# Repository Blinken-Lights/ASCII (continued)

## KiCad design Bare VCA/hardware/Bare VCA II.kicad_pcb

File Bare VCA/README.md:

# Bare VCA

Basic linear VCA based on LM13700. Similar to many schematics out there - but set up the way I like it.

6 x VCA and mixer, with built in clipping warning LEDs on the master output.

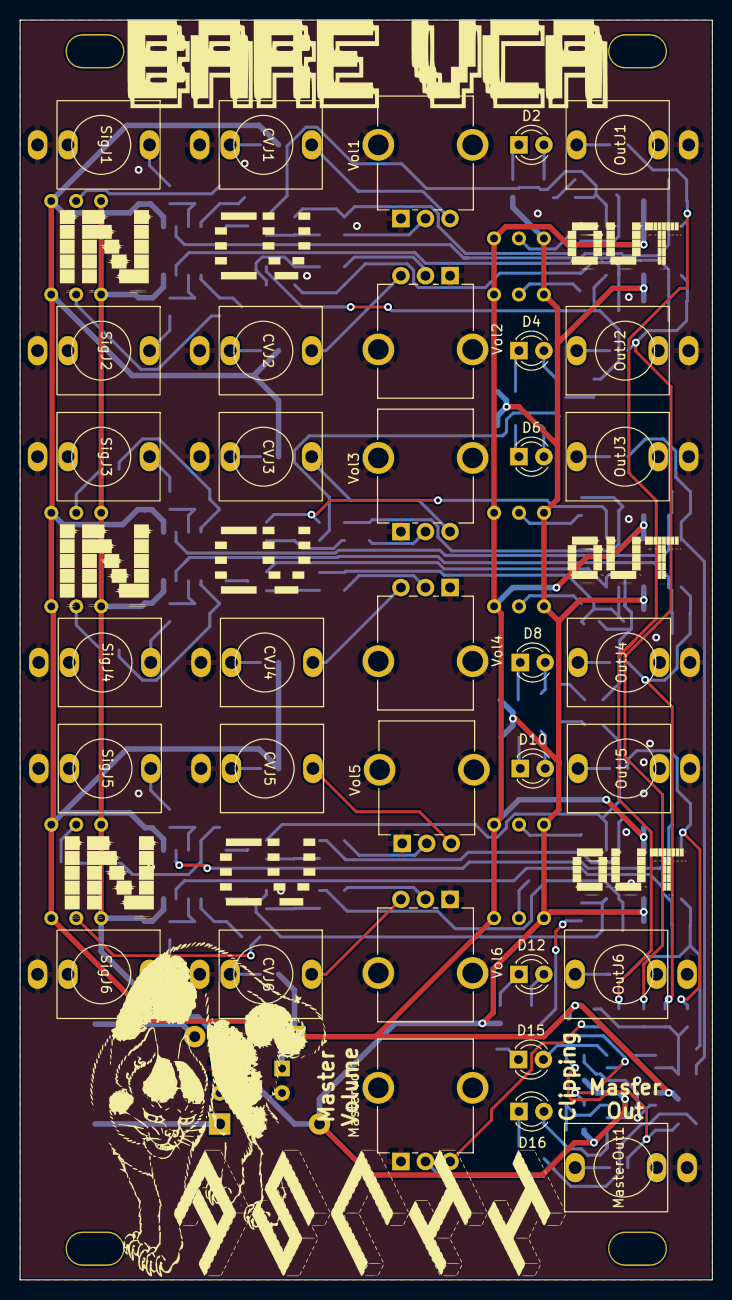
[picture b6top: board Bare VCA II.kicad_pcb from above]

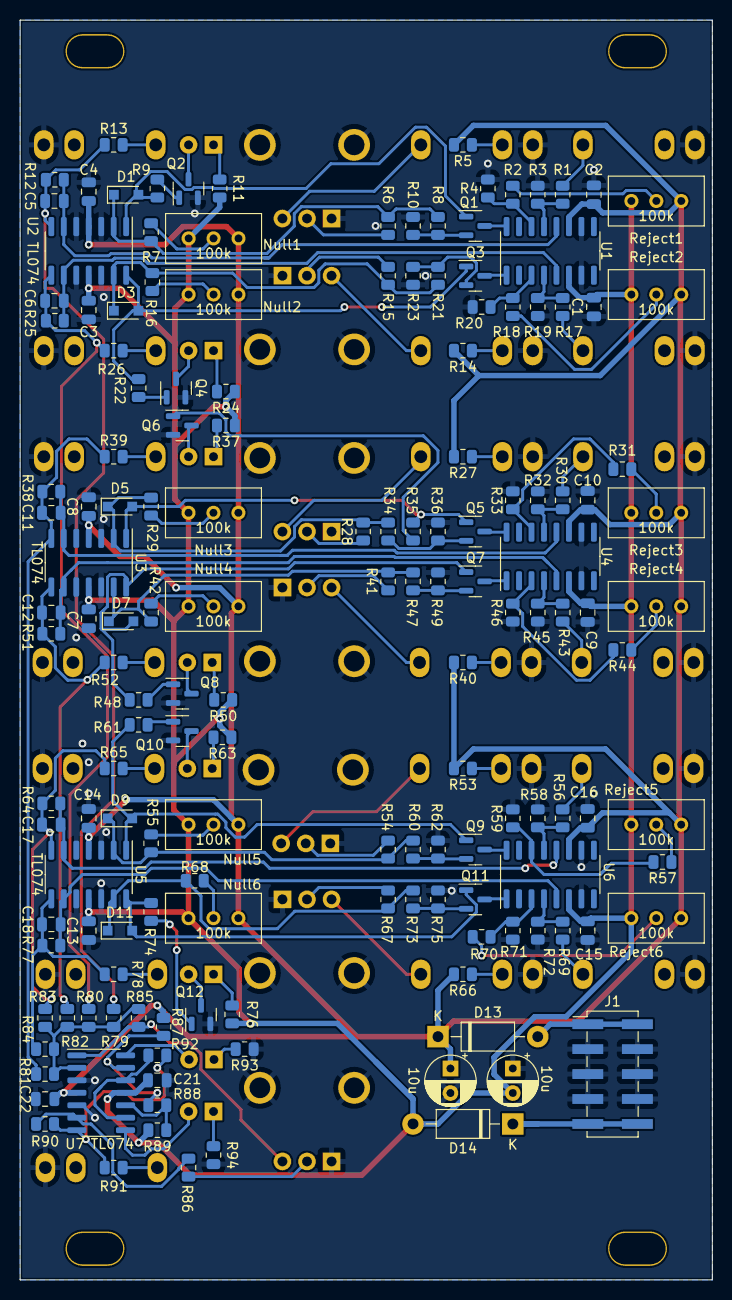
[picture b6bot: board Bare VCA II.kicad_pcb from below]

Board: 2 copper layers, 70.5 x 128.3 mm, 190 parts (156 on the bottom side), 126 nets.

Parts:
C1, C2, C3, C4, C7, C8, C9, C10, C13, C14, C15, C16, C21, C22: 100n; C_0805_2012Metric
C5, C6, C11, C12, C17, C18: 47p; C_0805_2012Metric
C19, C20: 10u; CP_Radial_D5.0mm_P2.50mm
CVJ1, CVJ2, CVJ3, CVJ4, CVJ5, CVJ6: Thonkiconn
D1, D3, D5, D7, D9, D11: 1N4148WS; D_SOD-323_HandSoldering
D2, D6, D10, D15: Red LED; LED_D3.0mm
D4, D8, D12, D16: Blue LED; LED_D3.0mm
D13, D14: 1N5817; D_DO-41_SOD81_P10.16mm_Horizontal
J1: Power; PinHeader_2x05_P2.54mm_Vertical_SMD
MasterOut1: Thonkiconn
MasterVol1: 100k; Potentiometer_GND_Alpha_RD901F-40-00D_Single_Vertical_Circu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
Null1, Null2, Null3, Null4, Null5, Null6: 100k; Potentiometer_Bourns_3296W_Vertical
OutJ1, OutJ2, OutJ3, OutJ4, OutJ5, OutJ6: Thonkiconn
Q1, Q2, Q3, Q4, Q5, Q6, Q7, Q8, Q9, Q10, Q11, Q12: MMBT3906; SOT-23
R1, R2, R6, R8, R12, R15, R17, R18, R21, R25, R28, R30, R31, R34, R38, R41, R43, R44, R47, R51, R54, R56, R57, R60, R64, R67, R69, R70, R73, R77, R79, R80, R81, R82, R83, R84, R86, R87, R89, R92: 100k; R_0805_2012Metric
R3, R4, R19, R20, R32, R33, R45, R46, R58, R59, R71, R72: 220; R_0805_2012Metric
R5, R14, R27, R40, R53, R66: 68k; R_0805_2012Metric
R7, R16, R29, R42, R55, R68: 200k; R_0805_2012Metric
R9, R22, R35, R48, R61, R74: 270k; R_0805_2012Metric
R10, R23, R36, R49, R62, R75: 22k; R_0805_2012Metric
R11, R24, R37, R50, R63, R76: 560; R_0805_2012Metric
R13, R26, R39, R52, R65, R78, R91: 1k; R_0805_2012Metric
R85: 33k; R_0805_2012Metric
R88: 820k; R_0805_2012Metric
R90: 330k; R_0805_2012Metric
R93, R94: 10k; R_0805_2012Metric
Reject1, Reject2, Reject3, Reject4, Reject5, Reject6: 100k; Potentiometer_Bourns_3296W_Vertical
SigJ1, SigJ2, SigJ3, SigJ4, SigJ5, SigJ6: Thonkiconn
U1, U4, U6: LM13700; SOIC-16_3.9x9.9mm_P1.27mm
U2, U3, U5, U7: TL074; SOIC-14_3.9x8.7mm_P1.27mm
Vol1, Vol2, Vol3, Vol4, Vol5, Vol6: 100k; Potentiometer_GND_Alpha_RD901F-40-00D_Single_Vertical_Circu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

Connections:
+12V: C2.1, C4.1, C8.1, C10.1, C14.1, C16.1, C19.1, C22.1, D13.1 (K), Null1.1, Null2.1, Null3.1, Null4.1, Null5.1, Null6.1, R5.2, R14.2, R27.2, R40.2, R53.2, R66.2, R87.2, Reject1.1, Reject2.1, Reject3.1, Reject4.1, Reject5.1, Reject6.1, U1.11 (V+), U2.4 (V+), U3.4 (V+), U4.11 (V+), U5.4 (V+), U6.11 (V+), U7.4 (V+)
-12V: C1.2, C3.2, C7.2, C9.2, C13.2, C15.2, C20.2, C21.2, D14.2 (A), Null1.3, Null2.3, Null3.3, Null4.3, Null5.3, Null6.3, R11.1, R24.1, R37.1, R50.1, R63.1, R76.1, R89.1, Reject1.3, Reject2.3, Reject3.3, Reject4.3, Reject5.3, Reject6.3, U1.6 (V-), U2.11 (V-), U3.11 (V-), U4.6 (V-), U5.11 (V-), U6.6 (V-), U7.11 (V-)
/2xVCAs1/CV In 1: CVJ3.3, Vol3.3
/2xVCAs1/CV In 2: CVJ4.3, Vol4.3
/2xVCAs1/Output 1: OutJ3.3, R39.2
/2xVCAs1/Output 2: OutJ4.3, R52.2
/2xVCAs1/Raw Output 1: C11.2, R38.2, R39.1, R81.1, U3.7
/2xVCAs1/Raw Output 2: C12.2, R51.2, R52.1, R82.1, U3.8
/2xVCAs1/Signal In 1: R30.1, SigJ3.3
/2xVCAs1/Signal In 2: R43.1, SigJ4.3
/2xVCAs2/CV In 1: CVJ5.3, Vol5.3
/2xVCAs2/CV In 2: CVJ6.3, Vol6.3
/2xVCAs2/Output 1: OutJ5.3, R65.2
/2xVCAs2/Output 2: OutJ6.3, R78.2
/2xVCAs2/Raw Output 1: C17.2, R64.2, R65.1, R83.1, U5.7
/2xVCAs2/Raw Output 2: C18.2, R77.2, R78.1, R84.1, U5.8
/2xVCAs2/Signal In 1: R56.1, SigJ5.3
/2xVCAs2/Signal In 2: R69.1, SigJ6.3
/2xVCAs/CV In 1: CVJ1.3, Vol1.3
/2xVCAs/CV In 2: CVJ2.3, Vol2.3
/2xVCAs/Output 1: OutJ1.3, R13.2
/2xVCAs/Output 2: OutJ2.3, R26.2
/2xVCAs/Raw Output 1: C5.2, R12.2, R13.1, R79.1, U2.7
/2xVCAs/Raw Output 2: C6.2, R25.2, R26.1, R80.1, U2.8
/2xVCAs/Signal In 1: R1.1, SigJ1.3
/2xVCAs/Signal In 2: R17.1, SigJ2.3
GND: C1.1, C2.2, C3.1, C4.2, C7.1, C8.2, C9.1, C10.2, C13.1, C14.2, C15.1, C16.2, C19.2, C20.1, C21.1, C22.2, CVJ1.1, CVJ2.1, CVJ3.1, CVJ4.1, CVJ5.1, CVJ6.1, J1.3, J1.4, J1.5, J1.6, J1.7, J1.8, MasterOut1.1, MasterVol1.1, MasterVol1.4 (GND), OutJ1.1, OutJ2.1, OutJ3.1, OutJ4.1, OutJ5.1, OutJ6.1, Q2.2 (E), Q4.2 (E), Q6.2 (E), Q8.2 (E), Q10.2 (E), Q12.2 (E), R3.1, R4.2, R10.2, R19.1, R20.2, R23.2, R32.1, R33.2, R36.2, R45.1, R46.2, R49.2, R58.1, R59.2, R62.2, R71.1, R72.2, R75.2, R93.1, R94.1, SigJ1.1, SigJ2.1, SigJ3.1, SigJ4.1, SigJ5.1, SigJ6.1, U1.7, U1.10, U2.3 (+), U2.5 (+), U2.10 (+), U2.12 (+), U3.3 (+), U3.5 (+), U3.10 (+), U3.12 (+), U4.7, U4.10, U5.3 (+), U5.5 (+), U5.10 (+), U5.12 (+), U6.7, U6.10, U7.3 (+), U7.5 (+), Vol1.1, Vol1.4 (GND), Vol2.1, Vol2.4 (GND), Vol3.1, Vol3.4 (GND), Vol4.1, Vol4.4 (GND), Vol5.1, Vol5.4 (GND), Vol6.1, Vol6.4 (GND)
unnamed: C5.1, R12.1, U1.12, U2.6 (-)
unnamed: C6.1, R25.1, U1.5, U2.9 (-)
unnamed: C11.1, R38.1, U3.6 (-), U4.12
unnamed: C12.1, R51.1, U3.9 (-), U4.5
unnamed: C17.1, R64.1, U5.6 (-), U6.12
unnamed: C18.1, R77.1, U5.9 (-), U6.5
unnamed: CVJ1.2, R5.1
unnamed: CVJ2.2, R14.1
unnamed: CVJ3.2, R27.1
unnamed: CVJ4.2, R40.1
unnamed: CVJ5.2, R53.1
unnamed: CVJ6.2, R66.1
unnamed: D1.1 (K), R6.2, R7.2, R8.1, U2.2 (-)
unnamed: D1.2 (A), Q1.1 (B), R9.1, U2.1
unnamed: D2.1 (K), R11.2
unnamed: D2.2 (A), Q2.3 (C)
unnamed: D3.1 (K), R15.2, R16.2, R21.1, U2.13 (-)
unnamed: D3.2 (A), Q3.1 (B), R22.1, U2.14
unnamed: D4.1 (K), R24.2
unnamed: D4.2 (A), Q4.3 (C)
unnamed: D5.1 (K), R28.2, R29.2, R34.1, U3.2 (-)
unnamed: D5.2 (A), Q5.1 (B), R35.1, U3.1
unnamed: D6.1 (K), R37.2
unnamed: D6.2 (A), Q6.3 (C)
unnamed: D7.1 (K), R41.2, R42.2, R47.1, U3.13 (-)
unnamed: D7.2 (A), Q7.1 (B), R48.1, U3.14
unnamed: D8.1 (K), R50.2
unnamed: D8.2 (A), Q8.3 (C)
unnamed: D9.1 (K), R54.2, R55.2, R60.1, U5.2 (-)
unnamed: D9.2 (A), Q9.1 (B), R61.1, U5.1
unnamed: D10.1 (K), R63.2
unnamed: D10.2 (A), Q10.3 (C)
unnamed: D11.1 (K), R67.2, R68.2, R73.1, U5.13 (-)
unnamed: D11.2 (A), Q11.1 (B), R74.1, U5.14
unnamed: D12.1 (K), R76.2
unnamed: D12.2 (A), Q12.3 (C)
unnamed: D13.2 (A), J1.1, J1.2
unnamed: D14.1 (K), J1.9, J1.10
unnamed: D15.1 (K), R93.2
unnamed: D15.2 (A), U7.14
unnamed: D16.1 (K), R94.2
unnamed: D16.2 (A), U7.8
unnamed: MasterOut1.3, R91.2
unnamed: MasterVol1.2, R86.1
unnamed: MasterVol1.3, R85.2, U7.1
unnamed: Null1.2, R7.1
unnamed: Null2.2, R16.1
unnamed: Null3.2, R29.1
unnamed: Null4.2, R42.1
unnamed: Null5.2, R55.1
unnamed: Null6.2, R68.1
unnamed: Q1.2 (E), R8.2, R10.1
unnamed: Q1.3 (C), U1.16
unnamed: Q2.1 (B), R9.2
unnamed: Q3.2 (E), R21.2, R23.1
unnamed: Q3.3 (C), U1.1
unnamed: Q4.1 (B), R22.2
unnamed: Q5.2 (E), R34.2, R36.1
unnamed: Q5.3 (C), U4.16
unnamed: Q6.1 (B), R35.2
unnamed: Q7.2 (E), R47.2, R49.1
unnamed: Q7.3 (C), U4.1
unnamed: Q8.1 (B), R48.2
unnamed: Q9.2 (E), R60.2, R62.1
unnamed: Q9.3 (C), U6.16
unnamed: Q10.1 (B), R61.2
unnamed: Q11.2 (E), R73.2, R75.1
unnamed: Q11.3 (C), U6.1
unnamed: Q12.1 (B), R74.2
unnamed: R1.2, R3.2, U1.13 (-)
unnamed: R2.1, Reject1.2
unnamed: R2.2, R4.1, U1.14 (+)
unnamed: R6.1, Vol1.2
unnamed: R15.1, Vol2.2
unnamed: R17.2, R19.2, U1.4 (-)
unnamed: R18.1, Reject2.2
unnamed: R18.2, R20.1, U1.3 (+)
unnamed: R28.1, Vol3.2
unnamed: R30.2, R32.2, U4.13 (-)
unnamed: R31.1, Reject3.2
unnamed: R31.2, R33.1, U4.14 (+)
unnamed: R41.1, Vol4.2
unnamed: R43.2, R45.2, U4.4 (-)
unnamed: R44.1, Reject4.2
unnamed: R44.2, R46.1, U4.3 (+)
unnamed: R54.1, Vol5.2
unnamed: R56.2, R58.2, U6.13 (-)
unnamed: R57.1, Reject5.2
unnamed: R57.2, R59.1, U6.14 (+)
unnamed: R67.1, Vol6.2
unnamed: R69.2, R71.2, U6.4 (-)
unnamed: R70.1, Reject6.2
unnamed: R70.2, R72.1, U6.3 (+)
unnamed: R79.2, R80.2, R81.2, R82.2, R83.2, R84.2, R85.1, U7.2 (-)
unnamed: R86.2, R90.1, U7.6 (-)
unnamed: R87.1, R88.2, U7.13 (-)
unnamed: R88.1, R89.2, U7.10 (+)
unnamed: R90.2, R91.1, R92.1, U7.7
unnamed: R92.2, U7.9 (-), U7.12 (+)

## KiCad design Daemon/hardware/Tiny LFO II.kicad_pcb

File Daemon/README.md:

# DAEMON

> In multitasking computer operating systems, a daemon (/ˈdiːmən/ or /ˈdeɪmən/)[1] is a computer program that runs as a background process, rather than being under the direct control of an interactive user.

Wikipedia contributors. "Daemon (computing)." Wikipedia, The Free Encyclopedia. Wikipedia, The Free Encyclopedia, 1 May. 2021. Web. 25 May. 2021.

'Daemon' is a cool sounding word, but it's also an appropriate description of this module.

It's intended to be the most stripped down and cheapest multifunction module possible, at the opposite end of the spectrum to eg. Ornament and Crime or Disting.

'Daemon' is based on a cheap and tiny microcontroller, the ATTiny85, and if you want an even more stripped down experience, the ATTiny45 can be used instead.

CV inputs are as basic as possible - just straight in to the analogue inputs of the μC with Schottky diodes as over voltage protection. 2 of the 3 CV inputs have passive attenuators (potentiometers) and are normalled to +V so can double as on-board knob inputs.

CV is output via PWM buffered through an op-amp. The ATTiny85 has fairly good fast PWM, so audio rate waveforms can be output acceptably. Both CV channels are hooked up to LEDs for some visual feedback.

CV in/output range is from 0 to 5V.

All 5 CV inputs can be reassigned as digital in/outputs if that fits the sketch that's running.

Finally, the reset pin is hooked up to a push button on the board. The ATTiny85 is able to remember how many times it's been reset, which can be exploited to, for example, page through different functions. That choice will be remembered when the module is powered back on.

Possible applications (of which I have coded NONE so far!) are:

- LFO .. single or dual, syncable, voltage controllable, different waveforms ETC..
- VCO .. reasonable 1V/Oct tracking should be possible
- Quantiser .. as above, should be enough accuracy on the in/out CV to track properly
- Bernoulli Gate
- Sample and Hold
- Envelope Generator .. EG voltage controlled AR or AD
- Clock Divider / Multiplier with 2 voltage controlled divisions from one clock input

This repo contains BOM and part position files that should be compatible with JLCPCB.

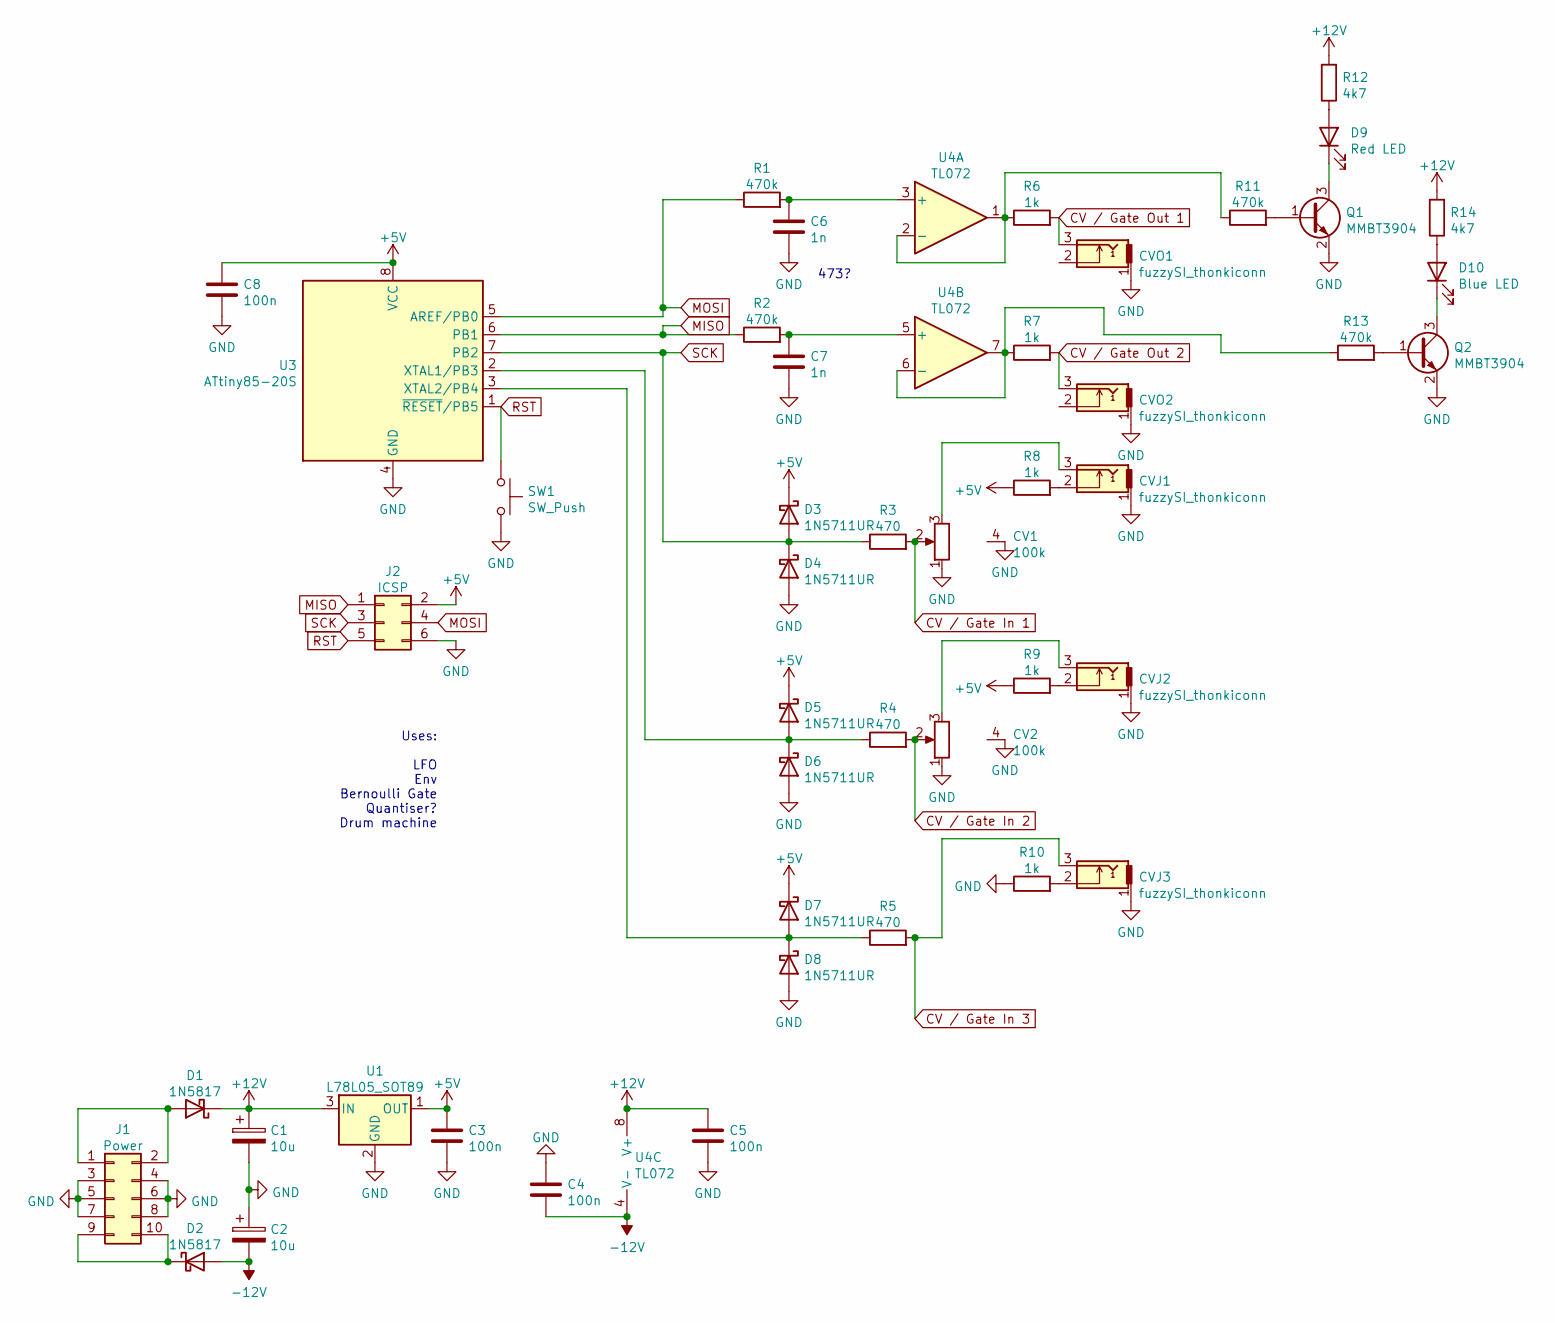
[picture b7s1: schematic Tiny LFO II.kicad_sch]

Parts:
C1, C2: 10u; CP_Radial_D5.0mm_P2.50mm
C3, C4, C5, C8: 100n; C_0805_2012Metric; LCSC C49678
C6, C7: 1n; C_0805_2012Metric; LCSC C46653
CV1, CV2: 100k; Potentiometer_GND_Alpha_RD901F-40-00D_Single_Vertical_Circu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
CVJ1, CVJ2, CVJ3: fuzzySI_thonkiconn; Thonkiconn
CVO1, CVO2: fuzzySI_thonkiconn; Thonkiconn
D1, D2: 1N5817; D_DO-41_SOD81_P10.16mm_Horizontal
D3, D4, D5, D6, D7, D8: 1N5711UR; D_SOD-323_HandSoldering; LCSC C151442
D9: Red LED; LED_D3.0mm; LCSC C84270
D10: Blue LED; LED_D3.0mm; LCSC C375460
J1: Power; PinHeader_2x05_P2.54mm_Vertical
J2: ICSP; PinHeader_2x03_P2.54mm_Vertical
Q1, Q2: MMBT3904; SOT-23; LCSC C20526
R1, R2, R11, R13: 470k; R_0805_2012Metric; LCSC C17709
R3, R4, R5: 470; R_0805_2012Metric; LCSC C17710
R6, R7, R8, R9, R10: 1k; R_0805_2012Metric; LCSC C17513
R12, R14: 4k7; R_0805_2012Metric; LCSC C17673
SW1: SW_Push; SW_PUSH_6mm; LCSC C127509
U1: L78L05_SOT89; SOT-89-3; LCSC C71136
U3: ATtiny85-20S; DIP-8_W7.62mm_Socket_LongPads; LCSC C89852
U4: TL072; SO-8_3.9x4.9mm_P1.27mm; LCSC C6961

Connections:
+5V: C3.1, C8.1, D3.1 (K), D5.1 (K), D7.1 (K), J2.2, R8.1, R9.1, U1.1 (OUT), U3.8 (VCC)
+12V: C1.1, C5.1, D1.1 (K), R12.2, R14.2, U1.3 (IN), U4.8 (V+)
-12V: C2.2, C4.2, D2.2 (A), U4.4 (V-)
CV / Gate In 1: CV1.2, R3.2
CV / Gate In 2: CV2.2, R4.2
CV / Gate In 3: CVJ3.3, R5.2
CV / Gate Out 1: CVO1.3, R6.2
CV / Gate Out 2: CVO2.3, R7.2
GND: C1.2, C2.1, C3.2, C4.1, C5.2, C6.2, C7.2, C8.2, CV1.1, CV1.4 (GND), CV2.1, CV2.4 (GND), CVJ1.1, CVJ2.1, CVJ3.1, CVO1.1, CVO2.1, D4.2 (A), D6.2 (A), D8.2 (A), J1.3, J1.4, J1.5, J1.6, J1.7, J1.8, J2.6, Q1.2 (E), Q2.2 (E), R10.1, SW1.2, U1.2 (GND), U3.4 (GND)
MISO: J2.1, R2.1, U3.6 (PB1)
MOSI: J2.4, R1.1, U3.5 (AREF/PB0)
unnamed: C6.1, R1.2, U4.3 (+)
unnamed: C7.1, R2.2, U4.5 (+)
unnamed: CV1.3, CVJ1.3
unnamed: CV2.3, CVJ2.3
unnamed: CVJ1.2, R8.2
unnamed: CVJ2.2, R9.2
unnamed: CVJ3.2, R10.2
unnamed: D1.2 (A), J1.1, J1.2
unnamed: D2.1 (K), J1.9, J1.10
unnamed: D5.2 (A), D6.1 (K), R4.1, U3.2 (XTAL1/PB3)
unnamed: D7.2 (A), D8.1 (K), R5.1, U3.3 (XTAL2/PB4)
unnamed: D9.1 (K), Q1.3 (C)
unnamed: D9.2 (A), R12.1
unnamed: D10.1 (K), Q2.3 (C)
unnamed: D10.2 (A), R14.1
unnamed: Q1.1 (B), R11.2
unnamed: Q2.1 (B), R13.2
unnamed: R6.1, R11.1, U4.1, U4.2 (-)
unnamed: R7.1, R13.1, U4.6 (-), U4.7
RST: J2.5, SW1.1, U3.1 (~RESET~/PB5)
SCK: D3.2 (A), D4.1 (K), J2.3, R3.1, U3.7 (PB2)

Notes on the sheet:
Uses: LFO Env Bernoulli Gate Quantiser? Drum machine
473?

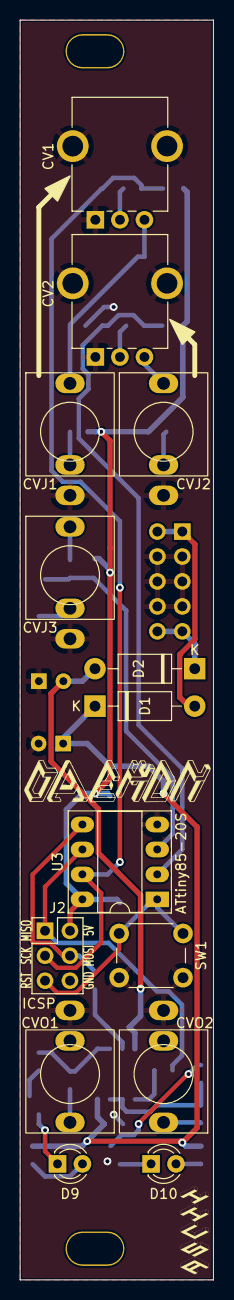
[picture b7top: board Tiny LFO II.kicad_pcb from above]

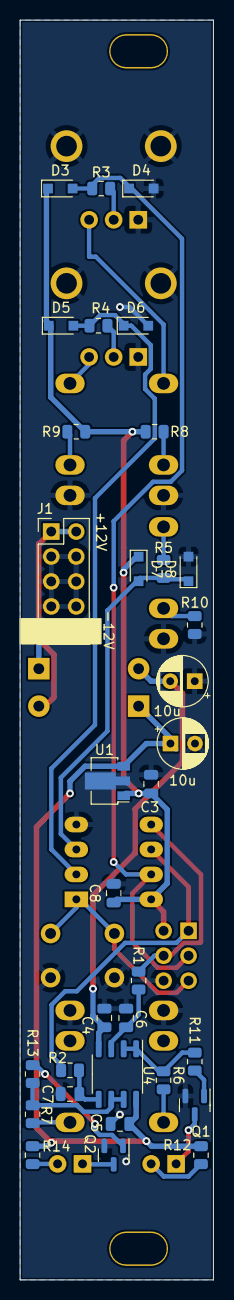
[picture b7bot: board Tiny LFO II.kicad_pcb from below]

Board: 2 copper layers, 19.7 x 128.3 mm, 47 parts (33 on the bottom side), 32 nets.

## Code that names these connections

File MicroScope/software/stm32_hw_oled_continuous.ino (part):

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STM32ADC myADC(ADC1);
uint16_t dataPoints[4];

Ucglib_SSD1351_18x128x128_HWSPI ucg(/*cd=*/ PB0, /*cs=*/ PA4, /*reset=*/ PB1);

//Ucglib_ST7735_18x128x160_HWSPI ucg(/*cd=*/ PB0, /*cs=*/ PA4, /*reset=*/ PB1);

/* tested working on chinese STM3

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
int h = 0;
// replace encoders with up/down buttons?
uint8 sensorPins[] = { PA0,  PA1,  PA2,  PA3 }; //{ PA0,  PA2,  PA6,  PB1 };
int a[4][512];
byte pa[4][128];
byte color[4][3] = {
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
//buttons
int debounce = 200;
int buttons[] = { PB12, PB13, PB14, PB15, PA8 };
unsigned long last_read[] = { 0, 0, 0, 0, 0 };
int presses[] = { 0, 0, 0, 0, 0 };
int dpresses[] = { 0, 0, 0, 0, 0 };
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  myADC.startConversion();

  for(int i = 0; i < 5; i++){
    pinMode(buttons[i], INPUT_PULLUP);   
  }
  attachInterrupt(digitalPinToInterrupt(buttons[0]),button0,FALLING);
  attachInterrupt(digitalPinToInterrupt(buttons[1]),button1,FALLING);
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
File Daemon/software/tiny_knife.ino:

/*
 * - 8 bit sample & hold:
 *   - In 1: channel 1
 *   - In 2: channel 2
 *   - In 3: trigger
 *   - Out 1: channel 1
 *   - Out 2: channel 2
 * 
 * 
 * - LFO:
 *   - In 1: Speed
 *   - In 2: Range OR Skew OR Shape?
 *   - In 3: Sync
 *   - Out 1: Tri/Saw/Sine etc 
 *   - Out 2: Square
 *
 * - ADR:
 * 
 * 
 * 
 * - Quantiser:
 * 
 * 
 * 
 * 
 * - Drum:
 * 
 * 
 * 
 * 
 * - VCO:
 * 
 * 
 */

#define F_CPU 8000000  // This is used by delay.h library

#include <avr/io.h>        // Adds useful constants
#include <util/delay.h>    // Adds delay_ms and delay_us functions
#include <EEPROM.h>

#define EXT_RESET (1 << EXTRF)

int count = 0;
int max_apps = 5;

byte pwm1 = 0;
byte pwm2 = 0;

void setup() {

  count = EEPROM.read(0);
  if(count >= max_apps){
    count = 0;
  }

  // borrowed from https://sites.google.com/site/wayneholder/using-the-avr-reset-pin-as-an-input 'Wayne's Tinkering Page'
  if ((MCUSR & EXT_RESET) != 0) {
    // If External RESET then increment count
    MCUSR = MCUSR & ~EXT_RESET;
    count++;
    if(count >= max_apps){
      count = 0;
    }
    EEPROM.write(0, count);
  }

  // setup different stuff depending on which app chosen by 'count'
  
  pinMode(0, OUTPUT); // OC0A
  pinMode(1, OUTPUT); // OC0B
  pinMode(2, INPUT); // Pot 1 - either input_pullup or analogue input
  pinMode(3, INPUT); // Pot 2
  pinMode(4, INPUT); // potential V/Oct

  // flash outputs to signify chosen app

  for(int i=0; i<count; i++){
    digitalWrite(0, HIGH);
    digitalWrite(1, HIGH);
    _delay_ms(125);
    digitalWrite(0, LOW);
    digitalWrite(1, LOW);
    _delay_ms(125);
  }
  _delay_ms(250);

  // The knobs normalled to 5V will glitch if another external cv input goes above/below 0-5V
  //      put it on different vreg / vref so it doesn't have a diode voltage added / removed from it
  // for audio-rate sampling
  ADCSRA = _BV(ADEN)    // enable the ADC
       | _BV(ADPS1)   // clock at
       | _BV(ADPS0);  //     F_CPU / 8 = 1 MHz
    
  // setup PWM if app needs it
  /*
  Control Register A for Timer/Counter-0 (Timer/Counter-0 is configured using two registers: A and B)
  TCCR0A is 8 bits: [COM0A1:COM0A0:COM0B1:COM0B0:unused:unused:WGM01:WGM00]
  2<<COM0A0: sets bits COM0A0 and COM0A1, which (in Fast PWM mode) clears OC0A on compare-match, and sets OC0A at BOTTOM
  2<<COM0B0: sets bits COM0B0 and COM0B1, which (in Fast PWM mode) clears OC0B on compare-match, and sets OC0B at BOTTOM
  3<<WGM00: sets bits WGM00 and WGM01, which (when combined with WGM02 from TCCR0B below) enables Fast PWM mode
  */
  TCCR0A = 2<<COM0A0 | 2<<COM0B0 | 3<<WGM00;
 
  /*
  Control Register B for Timer/Counter-0 (Timer/Counter-0 is configured using two registers: A and B)
  TCCR0B is 8 bits: [FOC0A:FOC0B:unused:unused:WGM02:CS02:CS01:CS00]
  0<<WGM02: bit WGM02 remains clear, which (when combined with WGM00 and WGM01 from TCCR0A above) enables Fast PWM mode
  1<<CS00: sets bits CS01 (leaving CS01 and CS02 clear), which tells Timer/Counter-0 to not use a prescalar
  */
  TCCR0B = 0<<WGM02 | 1<<CS00;

  OCR0A = 255;
  OCR0B = 255;

}

void loop() {

  /*
  // test sawtooth wave 
  OCR0A = pwm1;
  OCR0B = pwm1;
  pwm1++;

  _delay_ms(5);*/

  /*
  // test analogue inputs
  // 1 = PB2
  // 3 = PB3
  // 2 = PB4
  OCR0A = analogRead(1) >> 2; //PB2
  OCR0B = analogRead(3) >> 2; //PB3
  */

  //quantiser
  // to do - trigger.... should input 3 be normalled high too? - So quantisation is constant when nothing is plugged in
  //(void)analogRead(1);
  //_delay_ms(20);
  OCR0A = quantise(analogRead(1));
  //(void)analogRead(3);
  //_delay_ms(20);
  OCR0B = quantise(analogRead(3));

  //could do a single channel quantiser on IN3 where the other inputs are scale, and distance of CH2 note from the quantised one on CH1
  
}

byte quantise(int value){
  return round(min(60,round((float)((value >> 2) + 2) / 4.25)) * 4.25);
}

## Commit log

2021-06-11 Rename daemon_app_bundle.ino to daemon_app_bundle_v1.ino
2021-07-30 Create PCB
2022-10-26 Rename MicroScope_Rewrite_2022.ino to MicroScope_2022.ino
2022-10-29 Rename clock_divider_redesign.ino to Polyrhythms.ino
2022-10-29 Rename README.html to README.md
2022-11-26 Add comment with recommended Mozzi config
2023-02-15 Update README.md
    Add demo video
2025-05-06 Rename Pi Pico Clock-LFO.pdf to Pi Pico Clock-LFO-draft1.pdf
2025-05-06 Rename Pi Pico Clock-LFO-v0pt2.pdf to Pi Pico Clock-LFO-draft2.pdf
2025-05-06 Rename RP2350_MultiLFO.ino to PiPicoClockLFO-draft2.ino
